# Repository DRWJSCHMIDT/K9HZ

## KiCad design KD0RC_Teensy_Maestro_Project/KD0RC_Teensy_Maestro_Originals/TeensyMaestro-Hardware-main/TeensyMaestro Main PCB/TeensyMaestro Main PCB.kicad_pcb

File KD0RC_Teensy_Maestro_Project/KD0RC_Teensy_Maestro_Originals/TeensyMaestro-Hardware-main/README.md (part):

# TeensyMaestro Front Panel and PCB

### Summary
The TeensyMaestro is a custom-built hardware controller first designed by Len (KD0RC) to interface with FlexRadio transceivers - specifically models in the 6000 and 8000 series. It performs some, but not all, of the common functions that the SmartSDR app or the Flex Maestro perform. The name TeensyMaestro comes from its core component: the Teensy 4.1 microcontroller, which powers the device. Len's initial version was built using point-to-point wiring which presents a challenge for builders. Len (KD0RC) and Simon (NV0E) have created a PCB and matching front panel that simplifies the build process. Len's documentation for hardware version 1, along with firmware that supports all versions, is available here:

[TeensyMaestro for Flex 6000 Radios](https://github.com/KD0RC/Teensy-Maestro-for-Flex-6000-radios)

The intent of this PCB is to simplify the build process, make it easier to produce a polished final product, and replace some components with less expensive alternatives.

### Main PCB

### Design Features
- A main PCB that simplifies building the Teensy Maestro and minimizes wiring errors.
- A front panel that matches the main PCB that can be fabricated by a PCB manufacturer in aluminum, with a black finish. This inexpensive option will allow a builder to achieve a refined, professional finish.
- Through-hole components to simplify assembly.
- PCB headers to connect to the rear panel connectors.
- I2C bus header for future extensibility.
- Optocoupler on key-out connector for electrical isolation from the radio.
- Reduced BOM cost due to part substitution.

### Schematic Design

[Schematic Design](https://github.com/rimuadmin/TeensyMaestro-Hardware/blob/main/TeensyMaestro%20Main%20PCB/TeensyMaestro%20Main%20PCB.pdf)

### Circuit Differences from Original Design
- **Multiplexers (CD74HC5067M) → I2C I/O Expanders (MCP23008/MCP23017)** - This frees up some GPIOs on the Teensy for other uses.
- **Adafruit LCD (HX8357D) & Touch Controller (TSC2007) → ST7796S LCD** - The new LCD has an integrated touch controller, reducing cost from ~$45 to ~$19. It's also slightly larger (4.0" vs. 3.5”) but retains the same 480x320 resolution.
- **Panel-Mounted Switches → PCB-Mounted Switches** - The 4 panel mounted switches (RIT-A, XIT-A, RIT-B, XIT-B) are now directly mounted on the PCB.
- **Panel-Mounted Encoders → PCB-Mounted Encoders** - The 9 rotary encoders are now directly mounted on the PCB.
- An optocoupler has been added to the KEY OUT for electrical isolation between the TeensyMaestro and the radio.

# Ordering the PCB & Front Panel from JLCPCB

> Ordering the Main PCB and Front Panel in the same order will save on shipping costs.

### Add the Main PCB to the cart
1. Download the zip file (TeensyMaestro Main PCB/production/TeensyMaestro Main PCB_3.0.zip) from this repository to your PC
2. Open JLCPCB's web page (jlcpcb.com) in your browser
3. Click 'Order Now'
4. Use the 'Add gerber file' button to select the zip file that you downloaded
5. The order page will import the gerber files and you should see the 2D representation of the front and rear of the panel displayed.
6. JLCPCB examines the zip file and sets the Layers and Dimensions values.
7. The default quantity is 5, which is the minimum order quantity.
8. The remaining defaults don't need to be changed, but if you prefer a different color PCB you could select it here.
9. Optionally, select 'Surface Finish: LeadFree HASL'
10. Click 'Save to Cart'.

### Add the Front Panel to the cart
1. Download the zip file (TeensyMaestro Front Panel/production/TeensyMaestro_Front_Panel_v2.0.zip) from this repository to your PC.
2. Open JLCPCB's web page (jlcpcb.com) in a browser
3. Click 'Order Now'
4. Use the 'Add gerber file' button to select the zip file that you downloaded
5. The order page will import the gerber files and you should see the 2D representation of the front and rear of the panel displayed.
6. JLCPCB examines the zip file and sets the Layers and Dimensions values.
7. Select 'Base Material: Aluminum'
8. The default quantity is 5, which is the minimum order quantity.
9. Select 'PCB Color: Black'
10. Optionally, select 'Surface Finish: LeadFree HASL'
11. Select 'Mark on PCB: Remove Mark' *(If you don't remove this, the fabricator will print the order number on the front panel)*
12. Click 'Save to Cart'.

Check out and purchase the two boards.

# PCB Assembly Steps

> *Do not solder the display on to the front side of the PCB until all the components on the rear side of the PCB have been soldered. The display covers over component through-holes that can't be soldered after the display is in place.*

- The slice tuning encoders are attached directly to the front panel, with openings in the main PCB to allow the encoders to pass through.
- The front side of the PCB holds the display, encoders and push buttons.
- The reverse side of the PCB holds the Teensy 4.1 micro controller, I/O Expanders, header connectors, resistors and capacitors.

### 1. Prepare the Display

#### 1a. Remove the SD Card Holder from the Display
To fit all the necessary through-hole components onto the TeensyMaestro PCB, we had to fully utilize the available board space. One key adjustment involves removing the SD card holder that's built into the display module. There were several reasons for this:
- The SD card holder is not connected to the TeensyMaestro circuit, so it serves no functional purpose. 
- The metal casing of the SD card holder can short against the leads of through-hole components on the back of the PCB. 
- If left in place, it can cause the display to tilt or sit unevenly, making it difficult to mount the front panel flush.

**Steps to Remove the SD Card Holder:**
1. **Apply Flux** - Dab a small amount of flux on the joints to improve heat transfer and help the solder flow into the braid.
2. **Add Solder to the Joints** - Reflow the existing joints by adding a small amount of fresh solder to each one.
3. **Use Solder Wick** - Use solder wick to absorb the molten solder from each joint.
4. **Remove the Metal Cover** - While heating the corner joints with a soldering iron, gently pry up the metal cover of the SD card holder using tweezers. Don't apply excessive force or the solder pads will lift off the FR4 PCB material.
5. **Detach the Plastic Connector** - With the cover off, continue heating the pins while using tweezers to lift the plastic connector. 
6. **Clean the Area** - Use isopropyl alcohol and Q-tips to clean off any remaining flux or residue from the PCB.

#### 1b. Solder 4 Pin Header to Display
This 4-pin header is not used by the circuit, but must be added to provide mechanical support for the display on the PCB.

1. Count and mark a 4-pin section of a header strip.
2. Cut cleanly between the 4th and 5th pins.
3. Smooth edges with a file or sanding block if sharp or uneven.
4. Solder the 4 pin header to the left side of the display.
5. The pin headers on each side should now be the same height.

In this picture, the SD Card holder has been removed and the 4 pin header soldered to the left side of the display PCB:

### 2. Solder Male Headers to the Teensy 4.1

#### 2a. Prepare Two 24-Pin Headers for the Long Sides
1. Count and mark two 24-pin sections on a header strip.
2. Cut cleanly between the 24th and 25th pins.
3. Smooth edges with a file or sanding block if sharp or uneven.
4. Repeat for the second 24-pin header.

#### 2b. Create a 5-Pin Header for GND, PROG, and ON/OFF Pins
1. Count and cut a 5-pin section.
2. Check alignment: These 5 pins go on the short side of the Teensy, opposite the USB connector (above the SD card slot area).
3. Clean up the cut edge if needed.

#### 2c. Create a 1-Pin Header for VUSB
1. Cut a single pin from the strip.
2. Use pliers to gently remove any excess plastic or bent pins.

#### 2d. Solder Male Headers to the Teensy 4.1

### 3. Prepare Female Headers for the Teensy 4.1

#### 3a. Cut Two 24-Pin Female Headers
1. Count 25 pins on a header strip.
2. Cut on the 25th pin using side cutters. This preserves 24 usable sockets in the segment before the cut.
3. Trim plastic burrs from the cut end using a file or sandpaper if needed.
4. Repeat to create a second 24-pin female header.
5. Dry fit both on the long edges of the Teensy to verify alignment.

#### 3b. Cut a 5-Pin Header for GND, PROG, ON/OFF
1. Count 6 pins and cut on the 6th pin—this gives you a 5-socket segment.
2. Inspect and clean the edges to ensure all 5 sockets are usable.
3. This header will align with the 5-pin row near the SD card slot, opposite the USB port.

#### 3c. Cut a 1-Pin Header for VUSB
1. Cut on the 2nd pin to create a single-socket header.
2. Be gentle—cutting near the ends can sometimes crack or distort the housing.
3. Clean it up and confirm the pin is straight and usable.

### 4. Solder Female Headers to the PCB
1. Insert all female headers into your PCB in the correct locations.
2. Plug the Teensy into the headers (without soldering yet) to align everything flat and square.
3. Solder the headers to the PCB while the Teensy holds them in place. This helps prevent misalignment.
4. Once all headers are secure, remove the Teensy and finish your solder joints if needed.

### 5. Rear Side
1. Solder 2 x 18-pin IC sockets to the PCB. Check that the socket alignment matches the PCB footprint.
2. Solder 1 x 28-pin IC socket to the PCB. Check that the socket alignment matches the PCB footprint. Depending on the length of the socket leads, trim the leads to reduce the chance of the leads touching the back of the display.
3. Solder the opto-isolator to the PCB. Check the alignment to ensure the opto-isolator is oriented correctly.
4. Solder capacitors to the PCB.
5. Solder resistors to the PCB.
6. Solder header connectors to the PCB.

> *The 4 holes for the I2C expansion header are right next to the 4 pins for the display. Be careful to use the correct holes for the I2C connector.*

7. Carefully check all solder connections. The display will cover some components and you will not have another chance to correct some solder joints.

### 6. Front Side
1. Solder the encoders to the PCB.
2. Solder push button switches to the PCB.

### 7. Display
- *Check all rear side components have been mounted before this step.*
- Solder display to PCB. Be careful that the header pins are all evenly seated on the PCB. 

> The 4 left side pins are only required for mechanical support of the display on the PCB. If you prefer, only solder one of the four pins. If the display needs to be desoldered, there are 3 less pins to desolder.

### 8. Standoffs
- The standoffs are recommended to prevent the front panel from bowing when the small encoders are tightened against the PCB. 
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
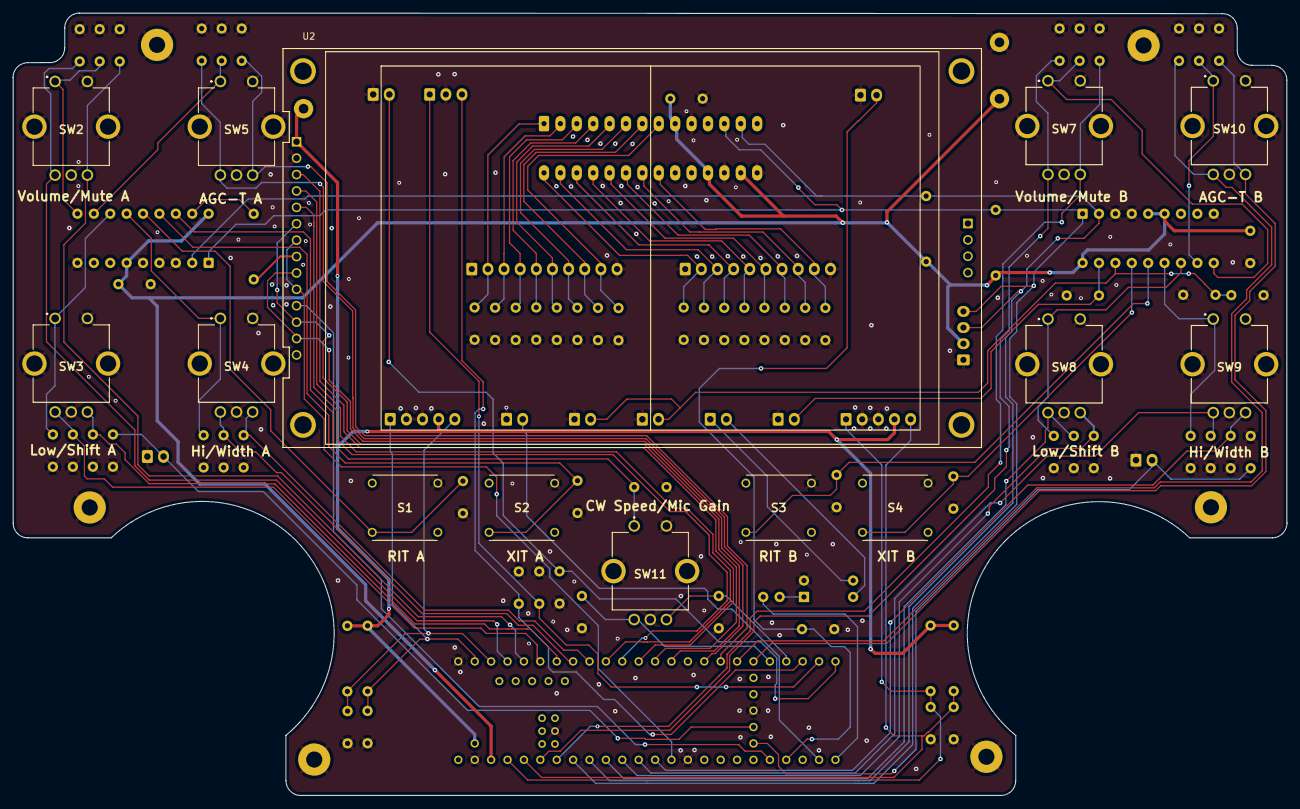
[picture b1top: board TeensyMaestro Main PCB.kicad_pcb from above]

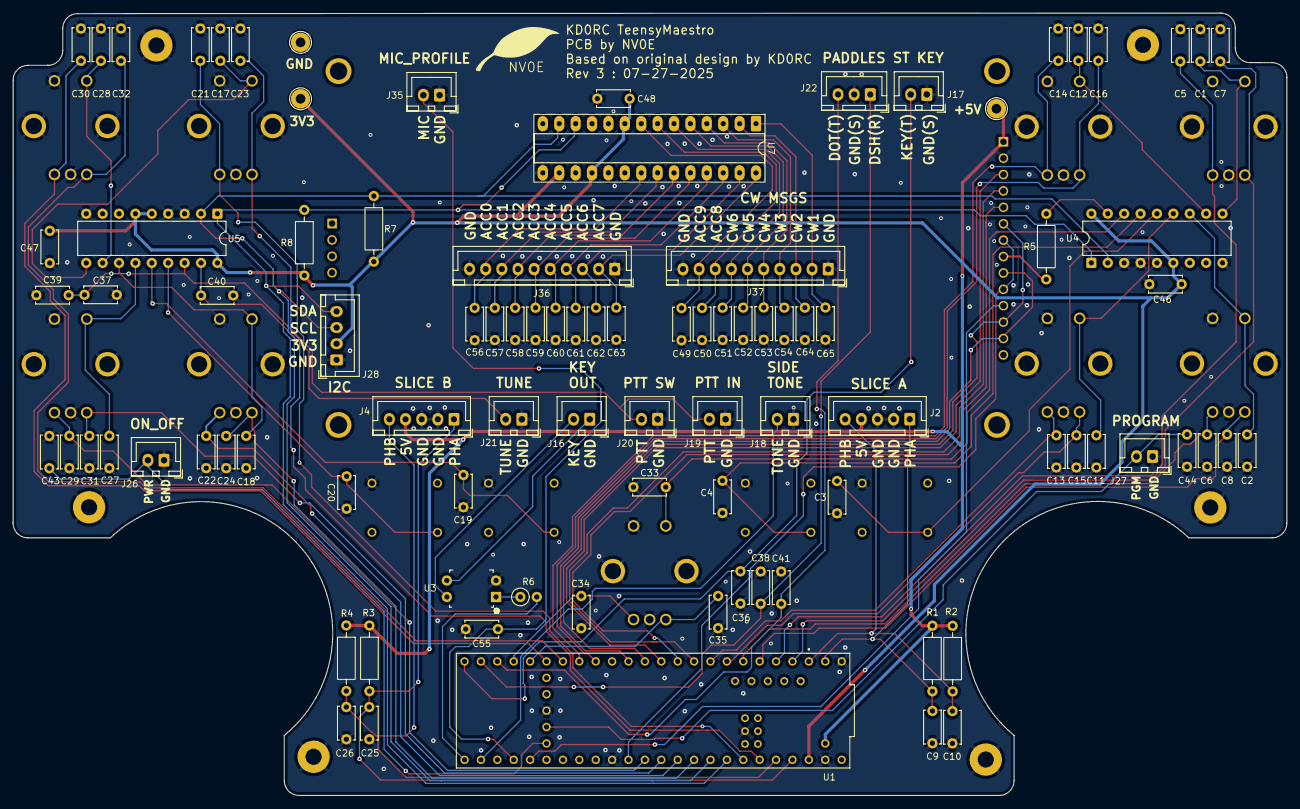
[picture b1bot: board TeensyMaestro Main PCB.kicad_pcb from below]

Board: 2 copper layers, 197.3 x 121.2 mm, 114 parts (94 on the bottom side), 78 nets.

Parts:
C1, C2, C3, C4, C5, C6, C7, C8, C9, C10, C11, C12, C13, C14, C15, C16, C17, C18, C19, C20, C21, C22, C23, C24, C25, C26, C27, C28, C29, C30, C31, C32, C33, C34, C35, C36, C37, C38, C39, C40, C41, C43, C44, C46, C47, C48, C49, C50, C51, C52, C53, C54, C55, C56, C57, C58, C59, C60, C61, C62, C63, C64, C65: 100nF; C_Disc_D5.0mm_W2.5mm_P5.00mm
H1, H2, H3, H4, H5, H6: MountingHole; MountingHole_2.5mm_Pad
J2, J4: B5B-XH-A_LF__SN_; JST_XH_B5B-XH-A_1x05_P2.50mm_Vertical
J16, J17, J18, J19, J20, J21, J26, J27, J35: B2B-XH-A_LF__SN_; JST_XH_B2B-XH-A_1x02_P2.50mm_Vertical
J22: B3B-XH-A_LF__SN_; JST_XH_B3B-XH-A_1x03_P2.50mm_Vertical
J28: B4B-PH-K-S_LF__SN_; JST_XH_B4B-XH-A_1x04_P2.50mm_Vertical
J36, J37: Conn_01x10; JST_XH_B10B-XH-A_1x10_P2.50mm_Vertical
R1, R2, R3, R4: 1K; R_Axial_DIN0207_L6.3mm_D2.5mm_P10.16mm_Horizontal
R5: 100; R_Axial_DIN0207_L6.3mm_D2.5mm_P10.16mm_Horizontal
R6: 1K; R_Axial_DIN0207_L6.3mm_D2.5mm_P2.54mm_Vertical
R7, R8: 4K7; R_Axial_DIN0207_L6.3mm_D2.5mm_P10.16mm_Horizontal
S1, S2, S3, S4: 1825910-6; 3ETH9120
SW2: RotaryEncoder_Switch_MP; PEC11L4115FS0020_NR
SW3: LowShift/NB A; PEC11L4115FS0020_NR
SW4: HighWidth/NR A; PEC11L4115FS0020_VNR
SW5: AGC-T/RIT_Sel A; PEC11L4115FS0020_VNR
SW7: Vol/Mute B; PEC11L4115FS0020_VNR
SW8: LowShift/NB B; PEC11L4115FS0020_VNR
SW9: HighWidth/NR B; PEC11L4115FS0020_NR
SW10: AGC-T/RIT_Sel A; PEC11L4115FS0020_NR
SW11: CW_Mic/Menu Sel; PEC11L4115FS0020
TP1: 5V; TestPoint_Loop_D2.54mm_Drill1.5mm_Beaded
TP2: 3V3; TestPoint_Loop_D2.54mm_Drill1.5mm_Beaded
TP3: GND; TestPoint_Loop_D2.54mm_Drill1.5mm_Beaded
U1: DEV-16771; MODULE_DEV-16771
U2: MSP4021-ST7796S; MSP4021-ST7796S-TM
U3: LTV-817; DIP-4_W7.62mm
U4, U5: MCP23008-xP; DIP-18_W7.62mm
U7: MCP23017-E_SP; DIP-28_W7.62mm_Socket_LongPads

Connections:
+3V3: C46.1, C47.1, C48.1, J28.2, R7.2, R8.2, TP2.1, U1.3.3V_2 (3.3V__1), U4.6 (~RESET), U4.18 (VDD), U5.5 (A0), U5.6 (~RESET), U5.18 (VDD), U7.9 (VDD), U7.16 (A1), U7.18 (~RESET)
+5V: J2.4, J4.4, R1.1, R2.1, R3.1, R4.1, TP1.1, U1.VUSB, U2.1 (VCC)
/IO Expander A/IOX_A_AGC-T1: C16.1, SW5.A, U1.24 (A10)
/IO Expander A/IOX_A_AGC-T2: C14.1, SW5.B, U1.25 (A11)
/IO Expander A/IOX_A_HIGH_WIDTH1: C15.1, SW4.A, U1.6 (OUT1D)
/IO Expander A/IOX_A_HIGH_WIDTH2: C13.1, SW4.B, U1.7 (RX2)
/IO Expander A/IOX_A_LOW_SHIFT1: C8.1, SW3.A, U1.4 (BCLK2)
/IO Expander A/IOX_A_LOW_SHIFT2: C6.1, SW3.B, U1.5 (IN2)
/IO Expander A/IOX_A_MUTE: C1.1, SW2.S1, U4.10 (GP0)
/IO Expander A/IOX_A_NB: C2.1, SW3.S1, U4.12 (GP2)
/IO Expander A/IOX_A_NR: C11.1, SW4.S1, U4.13 (GP3)
/IO Expander A/IOX_A_PhaseA: C9.1, J2.1, R1.2, U1.0 (RX1)
/IO Expander A/IOX_A_PhaseB: C10.1, J2.5, R2.2, U1.1 (TX1)
/IO Expander A/IOX_A_RIT: C3.1, S1.2, U4.14 (GP4)
/IO Expander A/IOX_A_RIT_SEL: C12.1, SW5.S1, U4.11 (GP1)
/IO Expander A/IOX_A_VOL1: C7.1, SW2.A, U1.2 (OUT2)
/IO Expander A/IOX_A_VOL2: C5.1, SW2.B, U1.3 (LRCLK2)
/IO Expander A/IOX_A_XIT: C4.1, S2.2, U4.15 (GP5)
/IO Expander A/MENU_SEL: C33.1, SW11.S1, U4.16 (GP6)
/IO Expander A/TFT_LED: R5.2, U4.17 (GP7)
/IO Expander B/IOX_B_AGC-T1: C32.1, SW10.A, U1.26 (A12)
/IO Expander B/IOX_B_AGC-T2: C30.1, SW10.B, U1.27 (A13)
/IO Expander B/IOX_B_HIGH_WIDTH1: C31.1, SW9.A, U1.15 (A1)
/IO Expander B/IOX_B_HIGH_WIDTH2: C29.1, SW9.B, U1.14 (A0)
/IO Expander B/IOX_B_LOW_SHIFT1: C24.1, SW8.A, U1.17 (A3)
/IO Expander B/IOX_B_LOW_SHIFT2: C22.1, SW8.B, U1.16 (A2)
/IO Expander B/IOX_B_MUTE: C17.1, SW7.S1, U5.10 (GP0)
/IO Expander B/IOX_B_NB: C18.1, SW8.S1, U5.12 (GP2)
/IO Expander B/IOX_B_NR: C27.1, SW9.S1, U5.13 (GP3)
/IO Expander B/IOX_B_PhaseA: C25.1, J4.1, R3.2, U1.23 (A9)
/IO Expander B/IOX_B_PhaseB: C26.1, J4.5, R4.2, U1.22 (A8)
/IO Expander B/IOX_B_RIT: C19.1, S3.2, U5.14 (GP4)
/IO Expander B/IOX_B_RIT_SEL: C28.1, SW10.S1, U5.11 (GP1)
/IO Expander B/IOX_B_VOL1: C23.1, SW7.A, U1.21 (A7)
/IO Expander B/IOX_B_VOL2: C21.1, SW7.B, U1.20 (A6)
/IO Expander B/IOX_B_XIT: C20.1, S4.2, U5.15 (GP5)
/IO Expander B/PTT: C37.1, C39.1, J19.2, J20.2, U5.16 (GP6)
/IO Expander B/TUNE: C40.1, J21.2, U5.17 (GP7)
/IO Expander C/ACC_0: C56.1, J36.9, U7.21 (GPA0)
/IO Expander C/ACC_1: C57.1, J36.8, U7.22 (GPA1)
/IO Expander C/ACC_2: C58.1, J36.7, U7.23 (GPA2)
/IO Expander C/ACC_3: C59.1, J36.6, U7.24 (GPA3)
/IO Expander C/ACC_4: C60.1, J36.5, U7.25 (GPA4)
/IO Expander C/ACC_5: C61.1, J36.4, U7.26 (GPA5)
/IO Expander C/ACC_6: C62.1, J36.3, U7.27 (GPA6)
/IO Expander C/ACC_7: C63.1, J36.2, U7.28 (GPA7)
/IO Expander C/ACC_8: C50.1, J37.8, U7.7 (GPB6)
/IO Expander C/ACC_9: C49.1, J37.9, U7.8 (GPB7)
/IO Expander C/CW_MSG_1: C65.1, J37.2, U7.1 (GPB0)
/IO Expander C/CW_MSG_2: C64.1, J37.3, U7.2 (GPB1)
/IO Expander C/CW_MSG_3: C54.1, J37.4, U7.3 (GPB2)
/IO Expander C/CW_MSG_4: C53.1, J37.5, U7.4 (GPB3)
/IO Expander C/CW_MSG_5: C52.1, J37.6, U7.5 (GPB4)
/IO Expander C/CW_MSG_6: C51.1, J37.7, U7.6 (GPB5)
/Mic Profile/MIC_PROFILE: C55.1, J35.2, U1.36 (CS2)
/Microcontroller/CW_MIC_MENU1: C35.1, SW11.A, U1.28 (RX7)
/Microcontroller/CW_MIC_MENU2: C34.1, SW11.B, U1.29 (TX7)
/Microcontroller/DASH: C38.1, J22.1, U1.31 (CTX3)
/Microcontroller/DOT: C41.1, J22.3, U1.30 (CRX3)
/Microcontroller/KEYOUT: R6.2, U1.33 (MCLK2)
/Microcontroller/LCD_CS: U1.10 (CS1), U2.3 (~CS)
/Microcontroller/ON_OFF: C43.1, J26.2, U1.ON/OFF
/Microcontroller/PROGRAM: C44.1, J27.2, U1.PROGRAM
/Microcontroller/SIDE_TONE: J18.2, U1.34 (RX8)
/Microcontroller/ST_KEY: C36.1, J17.2, U1.32 (OUT1B)
/Microcontroller/TFT_DC: U1.9 (OUT1C), U2.5 (D/~C)
/Microcontroller/TFT_MISO: U1.12 (MISO), U2.9 (MISO), U2.13 (T_DO)
/Microcontroller/TFT_MOSI: U1.11 (MOSI), U2.6 (MOSI), U2.12 (T_DIN)
/Microcontroller/TFT_RST: U1.8 (TX2), U2.4 (RESET)
/Microcontroller/TFT_SCK: U1.13 (SCK), U2.7 (SCK), U2.10 (T_CLK)
/Microcontroller/TOUCH_CS: U1.37 (CS3), U2.11 (T_CS)
/Miscellaneous/OPTO_COL: J16.2, U3.4
/Miscellaneous/OPTO_EMM: J16.1, U3.3
GND: C1.2, C2.2, C3.2, C4.2, C5.2, C6.2, C7.2, C8.2, C9.2, C10.2, C11.2, C12.2, C13.2, C14.2, C15.2, C16.2, C17.2, C18.2, C19.2, C20.2, C21.2, C22.2, C23.2, C24.2, C25.2, C26.2, C27.2, C28.2, C29.2, C30.2, C31.2, C32.2, C33.2, C34.2, C35.2, C36.2, C37.2, C38.2, C39.2, C40.2, C41.2, C43.2, C44.2, C46.2, C47.2, C48.2, C49.2, C50.2, C51.2, C52.2, C53.2, C54.2, C55.2, C56.2, C57.2, C58.2, C59.2, C60.2, C61.2, C62.2, C63.2, C64.2, C65.2, H1.1, H2.1, H3.1, H4.1, H5.1, H6.1, J2.2, J2.3, J4.2, J4.3, J17.1, J18.1, J19.1, J20.1, J21.1, J22.2, J26.1, J27.1, J28.1, J35.1, J36.1, J36.10, J37.1, J37.10, S1.4, S2.4, S3.4, S4.4, SW2.C, SW2.MP, SW2.S2, SW3.C, SW3.MP, SW3.S2, SW4.C, SW4.MP, SW4.S2, SW5.C, SW5.MP, SW5.S2, SW7.C, SW7.MP, SW7.S2, SW8.C, SW8.MP, SW8.S2, SW9.C, SW9.MP, SW9.S2, SW10.C, SW10.MP, SW10.S2, SW11.C, SW11.MP, SW11.S2, TP3.1, U1.GND1 (GND), U1.GND2 (GND__1), U1.GND3 (GND__2), U1.GND4 (GND__3), U1.GND5 (GND__4), U2.2 (GND), U3.2, U4.3 (A2), U4.4 (A1), U4.5 (A0), U4.9 (VSS), U5.3 (A2), U5.4 (A1), U5.9 (VSS), U7.10 (VSS), U7.15 (A0), U7.17 (A2)
I2C_SCL: J28.4, R8.1, U1.19 (A5), U4.1 (SCL), U5.1 (SCL), U7.12 (SCK)
I2C_SDA: J28.3, R7.1, U1.18 (A4), U4.2 (SDA), U5.2 (SDA), U7.13 (SDA)
unnamed: R6.1, U3.1
unnamed: R5.1, U2.8 (LED)

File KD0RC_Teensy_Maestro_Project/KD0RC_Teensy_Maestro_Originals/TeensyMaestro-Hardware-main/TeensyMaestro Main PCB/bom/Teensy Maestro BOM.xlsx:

Quantity | Designator | Description | Mouser | Digikey | Sparkfun | Other
63 | C1, C10, C11, C12, C13, C14, C15, C16, C17, C18, C19, C2, C20, C21, C22, C23, C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 | 0.1uF 50V Ceramic Leed Cap | 594-K104K15X7RF5WH5
9 | J16, J17, J18, J19, J20, J21, J26, J27, J35 | B2B-XH-A_LF__SN_ | 306-B2BXHALFSNP
2 | J2, J4 | B5B-XH-A_LF__SN_ | 306-B5BXHALFSN 306-B5BXHALFSN
1 | J22 | B3B-XH-A_LF__SN_ | 306-B3BXHALFSNP
1 | J28 | B4B-PH-K-S_LF__SN_ | 306-B4BXHALFSN
2 | J36, J37 | Conn_01x10 | 306-B10BXHALFSNP
5 | R1, R2, R3, R4, R6 | 1K Ohm 0.25W | 603-MFR-25FBF52-1K
1 | R5 | 100 Ohm 0.25W | 603-MFR-25FTF52-100R
2 | R7, R8 | 4K7 Ohm 0.25W | 603-MFR-25FRF52-4K7
4 | S1, S2, S3, S4 | SPST Momentary Switch | 642-3ETH9-12.0 | 679-3734-ND
11 | SW1, SW2, SW3, SW4, SW5, SW6, SW7, SW8, SW9, SW10, SW11 | PEC11L4115FS0020 Encoder | 652-PEC11L4115FS0020
3 | TP1, TP2, TP3 | IDC Test Pin/ Loop |  |  |  | TaydaElectronics
1 | U1 | Teensy 4.1 w/ Ethernet |  |  | DEV-16771
1 | U2 | 4" Display w/ ST7796S |  |  |  | eBay
1 | U3 | LTV-817 | 859-LTV-817
2 | U4, U5 | MCP23008-xP | 579-MCP23008-E/P
1 | U7 | MCP23017-E_SP | 579-MCP23017-E/SP

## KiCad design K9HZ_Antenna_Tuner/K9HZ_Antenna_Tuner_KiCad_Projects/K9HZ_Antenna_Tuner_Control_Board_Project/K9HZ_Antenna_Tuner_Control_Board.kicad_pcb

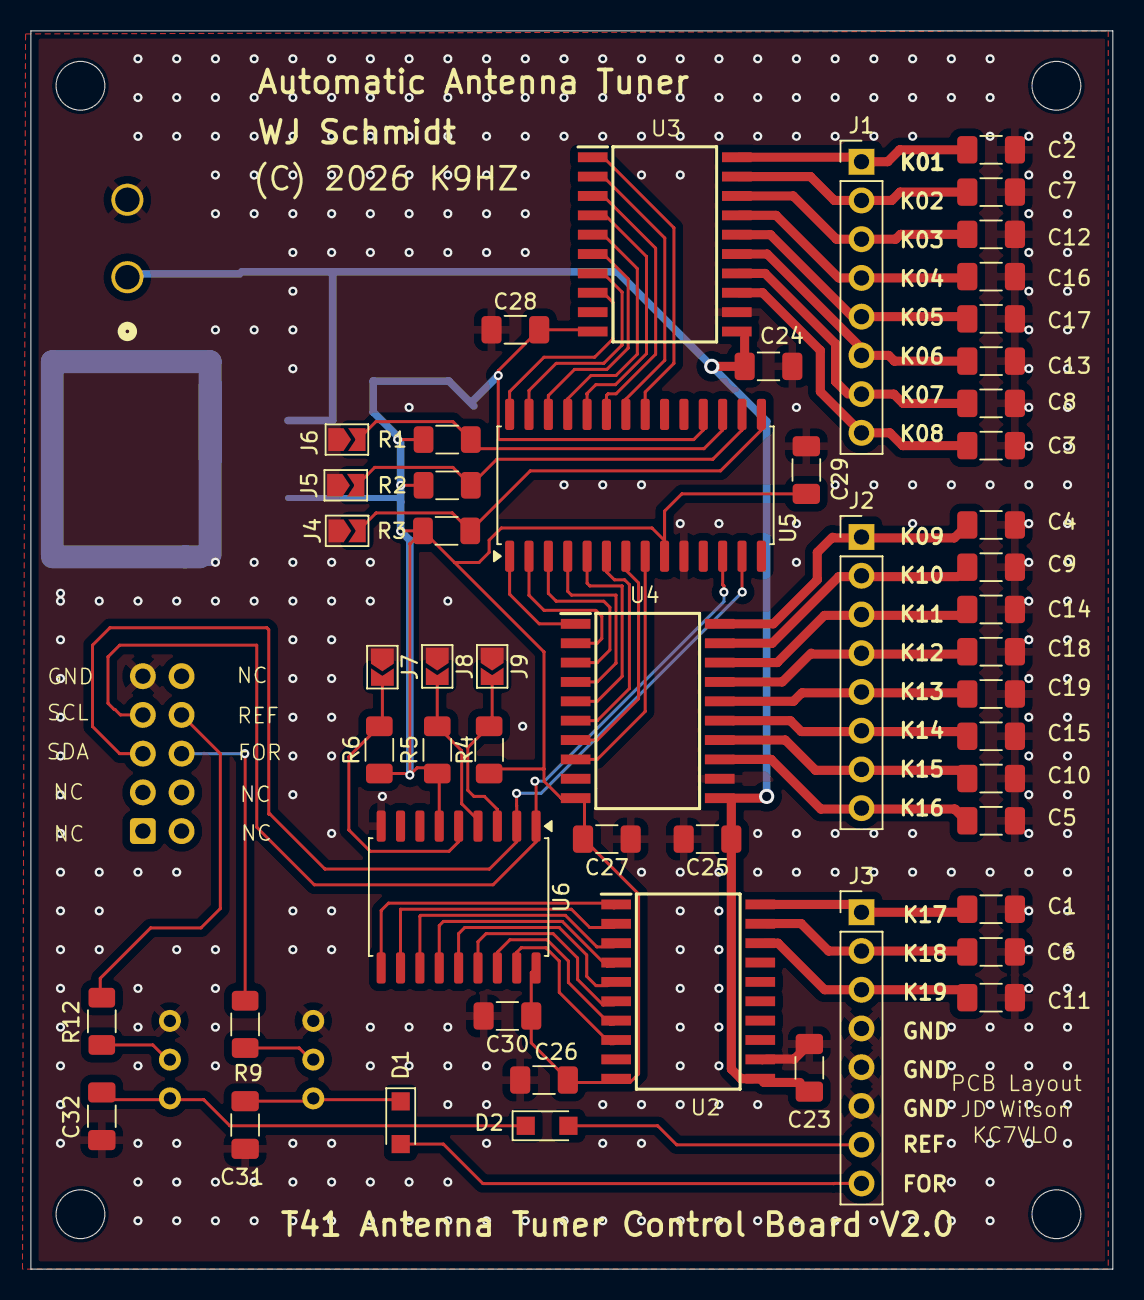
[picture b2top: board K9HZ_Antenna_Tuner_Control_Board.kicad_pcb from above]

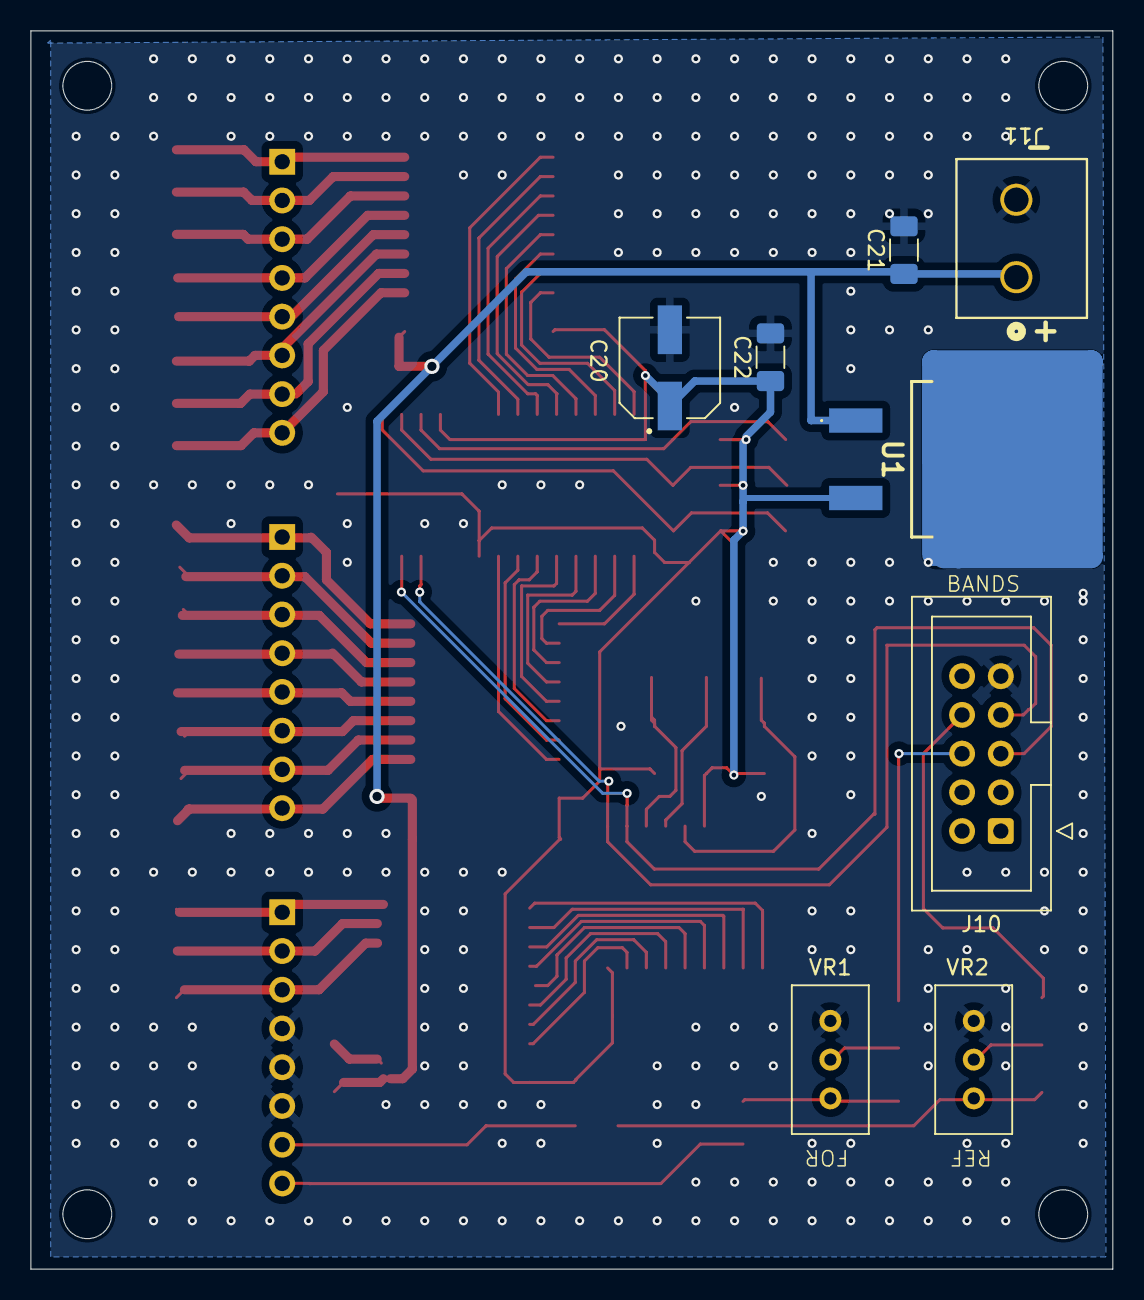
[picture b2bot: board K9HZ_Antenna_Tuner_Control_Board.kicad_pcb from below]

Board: 2 copper layers, 70.9 x 81.2 mm, 65 parts (8 on the bottom side), 62 nets.

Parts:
C1, C2, C3, C4, C5, C6, C7, C8, C9, C10, C11, C12, C13, C14, C15, C16, C17, C18, C19, C23, C24, C25, C26, C27, C28, C29, C30: 0.1uf 50V; C_1206_3216Metric_Pad1.33x1.80mm_HandSolder
C20: 220uf 16V; CAP_EEEFK1C221XP
C21: 1uf 25V; C_1206_3216Metric_Pad1.33x1.80mm_HandSolder
C22: 1uf 16V; C_1206_3216Metric_Pad1.33x1.80mm_HandSolder
C31, C32: 0.01uf 50V; C_1206_3216Metric_Pad1.33x1.80mm_HandSolder
D1, D2: BAS70H,115; Nexperia_CFP3_SOD-123W
H1, H2, H3, H4: MountingHole; MountingHole_3.2mm_M3
J1, J2, J3: 1986717-8; PinHeader_1x08_P2.54mm_Vertical
J4, J7: A0; SolderJumper-2_P1.3mm_Open_TrianglePad1.0x1.5mm
J5, J8: A1; SolderJumper-2_P1.3mm_Open_TrianglePad1.0x1.5mm
J6, J9: A2; SolderJumper-2_P1.3mm_Open_TrianglePad1.0x1.5mm
J10: IDC2x5; IDC-Header_2x05_P2.54mm_Vertical
J11: 395310002; CONN_SD-39531-003_02P_MOL
R1, R2, R3, R4, R5, R6: 3.3K; R_1206_3216Metric_Pad1.30x1.75mm_HandSolder
R9, R12: 10K; R_1206_3216Metric_Pad1.30x1.75mm_HandSolder
U1: L7805ABD2T-TR; L7805ABD2TTR
U2, U3, U4: UDN2987LWTR-6-T; SOIC127P1030X265-20N
U5: MCP23017_SO; SOIC-28W_7.5x17.9mm_P1.27mm
U6: MCP23008-E/SO; SOIC-18W_7.5x11.6mm_P1.27mm
VR1, VR2: 22k; Potentiometer_Bourns_3296W_Vertical

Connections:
+5V: C20.1, C22.1, C26.2, C27.2, C28.2, C29.1, C30.1, R1.1, R2.1, R3.1, R4.1, R5.1, R6.1, U1.3 (OUTPUT), U2.10 (OE/~R), U3.10 (OE/~R), U4.10 (OE/~R), U5.9 (VDD), U5.18 (~RESET), U6.6 (~RESET), U6.18 (VDD)
+12V: C21.1, C23.1, C24.1, C25.1, J11.1, U1.1 (INPUT), U2.11 (VS), U3.11 (VS), U4.11 (VS)
GND: C1.2, C2.2, C3.2, C4.2, C5.2, C6.2, C7.2, C8.2, C9.2, C10.2, C11.2, C12.2, C13.2, C14.2, C15.2, C16.2, C17.2, C18.2, C19.2, C20.2, C21.2, C22.2, C23.2, C24.2, C25.2, C26.1, C27.1, C28.1, C29.2, C30.2, C31.2, C32.2, J3.4, J3.5, J3.6, J4.1 (A), J5.1 (A), J6.1 (A), J7.1 (A), J8.1 (A), J9.1 (A), J10.9, J11.2, U1.2 (GND), U2.12 (GND), U3.12 (GND), U4.12 (GND), U5.10 (VSS), U6.9 (VSS), VR1.3, VR2.3
unnamed: D1.2 ((A)), J3.8
unnamed: C31.1, D1.1 ((C)), VR1.1
unnamed: D2.2 ((A)), J3.7
unnamed: C32.1, D2.1 ((C)), VR2.1
unnamed: C2.1, J1.1, U3.20 (OUT1)
unnamed: C7.1, J1.2, U3.19 (OUT2)
unnamed: C12.1, J1.3, U3.18 (OUT3)
unnamed: C16.1, J1.4, U3.17 (OUT4)
unnamed: C17.1, J1.5, U3.16 (OUT5)
unnamed: C13.1, J1.6, U3.15 (OUT6)
unnamed: C8.1, J1.7, U3.14 (OUT7)
unnamed: C3.1, J1.8, U3.13 (OUT8)
unnamed: C4.1, J2.1, U4.20 (OUT1)
unnamed: C9.1, J2.2, U4.19 (OUT2)
unnamed: C14.1, J2.3, U4.18 (OUT3)
unnamed: C18.1, J2.4, U4.17 (OUT4)
unnamed: C19.1, J2.5, U4.16 (OUT5)
unnamed: C15.1, J2.6, U4.15 (OUT6)
unnamed: C10.1, J2.7, U4.14 (OUT7)
unnamed: C5.1, J2.8, U4.13 (OUT8)
unnamed: C1.1, J3.1, U2.20 (OUT1)
unnamed: C6.1, J3.2, U2.19 (OUT2)
unnamed: C11.1, J3.3, U2.18 (OUT3)
unnamed: J4.2 (B), R3.2, U5.15 (A0)
unnamed: J5.2 (B), R2.2, U5.16 (A1)
unnamed: J6.2 (B), R1.2, U5.17 (A2)
unnamed: J7.2 (B), R6.2, U6.5 (A0)
unnamed: J8.2 (B), R5.2, U6.4 (A1)
unnamed: J9.2 (B), R4.2, U6.3 (A2)
unnamed: J10.5, U5.13 (SDA), U6.2 (SDA)
unnamed: J10.6, R9.1
unnamed: J10.7, U5.12 (SCL), U6.1 (SCL)
unnamed: J10.8, R12.1
unnamed: R9.2, VR1.2
unnamed: R12.2, VR2.2
unnamed: U2.1 (IN1), U6.10 (GP0)
unnamed: U2.2 (IN2), U6.11 (GP1)
unnamed: U2.3 (IN3), U6.12 (GP2)
unnamed: U2.4 (IN4), U6.13 (GP3)
unnamed: U2.5 (IN5), U6.14 (GP4)
unnamed: U2.6 (IN6), U6.15 (GP5)
unnamed: U2.7 (IN7), U6.16 (GP6)
unnamed: U2.8 (IN8), U6.17 (GP7)
unnamed: U3.1 (IN1), U5.21 (GPA0)
unnamed: U3.2 (IN2), U5.22 (GPA1)
unnamed: U3.3 (IN3), U5.23 (GPA2)
unnamed: U3.4 (IN4), U5.24 (GPA3)
unnamed: U3.5 (IN5), U5.25 (GPA4)
unnamed: U3.6 (IN6), U5.26 (GPA5)
unnamed: U3.7 (IN7), U5.27 (GPA6)
unnamed: U3.8 (IN8), U5.28 (GPA7)
unnamed: U4.1 (IN1), U5.1 (GPB0)
unnamed: U4.2 (IN2), U5.2 (GPB1)
unnamed: U4.3 (IN3), U5.3 (GPB2)
unnamed: U4.4 (IN4), U5.4 (GPB3)
unnamed: U4.5 (IN5), U5.5 (GPB4)
unnamed: U4.6 (IN6), U5.6 (GPB5)
unnamed: U4.7 (IN7), U5.7 (GPB6)
unnamed: U4.8 (IN8), U5.8 (GPB7)

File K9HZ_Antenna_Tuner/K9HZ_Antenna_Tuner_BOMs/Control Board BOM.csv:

#;Quantity;RefDes;Value;Name
1;1;C1;0.1uf 50V;CAP_1206
2;1;C2;0.1uf 50V;CAP_1206
3;1;C3;0.1uf 50V;CAP_1206
4;1;C4;0.1uf 50V;CAP_1206
5;1;C5;0.1uf 50V;CAP_1206
6;1;C6;0.1uf 50V;CAP_1206
7;1;C7;0.1uf 50V;CAP_1206
8;1;C8;0.1uf 50V;CAP_1206
9;1;C9;0.1uf 50V;CAP_1206
10;1;C10;0.1uf 50V;CAP_1206
11;1;C11;0.1uf 50V;CAP_1206
12;1;C12;0.1uf 50V;CAP_1206
13;1;C13;0.1uf 50V;CAP_1206
14;1;C14;0.1uf 50V;CAP_1206
15;1;C15;0.1uf 50V;CAP_1206
16;1;C16;0.1uf 50V;CAP_1206
17;1;C17;0.1uf 50V;CAP_1206
18;1;C18;0.1uf 50V;CAP_1206
19;1;C19;0.1uf 50V;CAP_1206
20;1;C20;220uf 16V;CAPAE_6.6x6.6h5.4
21;1;C21;1uF 25V;CAP_1206
22;1;C22;1uF 16V;CAP_1206
23;1;C23;0.1uf 50V;CAP_1206
24;1;C24;0.1uf 50V;CAP_1206
25;1;C25;0.1uf 50V;CAP_1206
26;1;C26;0.1uf 50V;CAP_1206
27;1;C27;0.1uf 50V;CAP_1206
28;1;C28;0.1uF 50V;CAP_1206
29;1;C29;0.1uf 50V;CAP_1206
30;1;C30;0.1uF 50V;CAP_1206
31;1;C31;0.01uF 50V;CAP_1206
32;1;C32;0.01uF 50V;CAP_1206
33;1;D1;;BAS70H,115
34;1;D2;;BAS70H,115
35;1;J1;;1986717-8
36;1;J2;;1986717-8
37;1;J3;;1986717-8
38;1;J4;;395310002
39;1;J5;BANDS;IDC2x5_Male
40;1;J6;;Solder_JMP_2
41;1;J7;;Solder_JMP_2
42;1;J8;;Solder_JMP_2
43;1;J9;;Solder_JMP_2
44;1;J10;;Solder_JMP_2
45;1;J11;;Solder_JMP_2
46;1;R1;3.3K Ohm;RES_1206
47;1;R2;3.3K Ohm;RES_1206
48;1;R3;3.3K Ohm;RES_1206
49;1;R4;3.3K Ohm;RES_1206
50;1;R5;3.3K Ohm;RES_1206
51;1;R6;3.3K Ohm;RES_1206
52;1;R7;22K;3296W
53;1;R8;52.3 Ohm;RES_1206
54;1;R9;10K;RES_0805
55;1;R10;22K;3296W
56;1;R11;52.3 Ohm;RES_1206
57;1;R12;10K;RES_1206
58;1;U1;;L7805ABD2T-TR
59;1;U2;;UDN2987LW
60;1;U3;;UDN2987LW
61;1;U4;;UDN2987LW
62;1;U5;;MCP23017_SO
63;1;U6;;MCP23008-E/SO

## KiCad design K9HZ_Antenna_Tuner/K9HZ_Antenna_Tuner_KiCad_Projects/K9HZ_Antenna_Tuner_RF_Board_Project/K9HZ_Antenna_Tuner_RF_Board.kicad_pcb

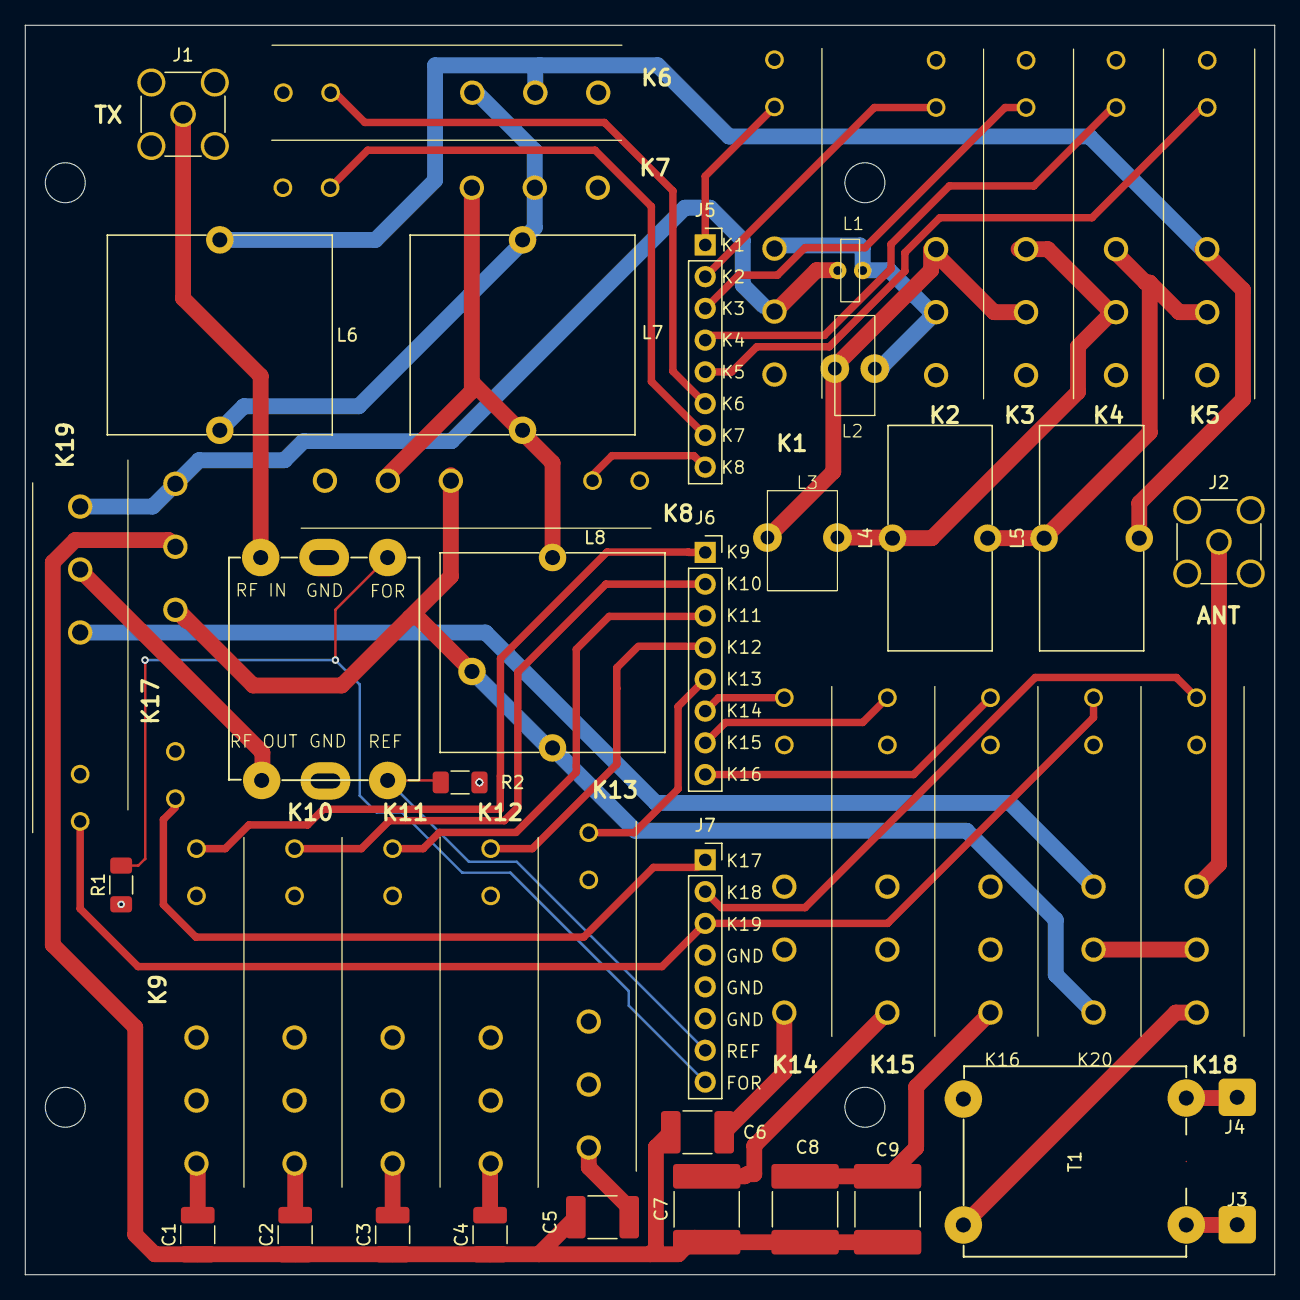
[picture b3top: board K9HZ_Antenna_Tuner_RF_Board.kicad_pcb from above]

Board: 2 copper layers, 100.0 x 100.0 mm, 52 parts (0 on the bottom side), 45 nets.

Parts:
C1: 10pF 500V; C_1210_3225Metric_Pad1.33x2.70mm_HandSolder
C2: 22pF 500V; C_1210_3225Metric_Pad1.33x2.70mm_HandSolder
C3: 47pF 500V; C_1210_3225Metric_Pad1.33x2.70mm_HandSolder
C4: 100pF 500V; C_1210_3225Metric_Pad1.33x2.70mm_HandSolder
C5: 220pF 500V; C_1812_4532Metric_Pad1.57x3.40mm_HandSolder
C6: 470pF 500V; C_1812_4532Metric_Pad1.57x3.40mm_HandSolder
C7, C8, C9: 1000pF 500V; C_2220_5750Metric_Pad1.97x5.40mm_HandSolder
H1, H2, H3, H4: MountingHole; MountingHole_3.2mm_M3
J1, J2: Conn_Coaxial; SMA_Amphenol_901-144_Vertical
J3, J4: Conn_01x01_Pin; SolderWire-0.1sqmm_1x01_D0.4mm_OD1mm
J5: 1986717-8; PinSocket_1x08_P2.54mm_Vertical
J6, J7: 1986717-8_8; PinSocket_1x08_P2.54mm_Vertical
K1, K2, K3, K4, K5, K6, K7, K8, K9, K10, K11, K12, K13, K14, K15, K16, K17, K18, K19, K20: HF41F_12-ZS; HF41F12ZS
L1: 0.05uH; L1
L2: 0.1uH; L2
L3: 0.22uH; L3
L4: 0.45uH; L_Toroid_Vertical_L17.8mm_W8.1mm_P7.62mm_Bourns_5700
L5: 1.00uH; L_Toroid_Vertical_L17.8mm_W8.1mm_P7.62mm_Bourns_5700
L6: 2.2uH; DoubleCoil
L7: 4.4uH; DoubleCoil
L8: 8.8uH; DoubleCoil
L44: Balun_5PIN_BN-43-202
R1, R2: 52.3 Ohm; R_1206_3216Metric_Pad1.30x1.75mm_HandSolder
T1: Transformer_SP_1S; Balun_5PIN_BN-43-202

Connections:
/Bypass: J7.3, K19.1 (COIL_1), K20.1 (COIL_1)
/K1.2: J5.1, K1.2 (COIL_2)
/K2.2: J5.2, K2.2 (COIL_2)
/K3.2: J5.3, K3.2 (COIL_2)
/K4.2: J5.4, K4.2 (COIL_2)
/K5.2: J5.5, K5.2 (COIL_2)
/K6.2: J5.6, K6.2 (COIL_2)
/K7.2: J5.7, K7.2 (COIL_2)
/K8.2: J5.8, K8.2 (COIL_2)
/K9.1: J6.1, K9.1 (COIL_1)
/K10.1: J6.2, K10.1 (COIL_1)
/K11.1: J6.3, K11.1 (COIL_1)
/K12.1: J6.4, K12.1 (COIL_1)
/K13.1: J6.5, K13.1 (COIL_1)
/K14.1: J6.6, K14.1 (COIL_1)
/K15.1: J6.7, K15.1 (COIL_1)
/K16.1: J6.8, K16.1 (COIL_1)
/K17.1: J7.1, K17.1 (COIL_1)
/K18.1: J7.2, K18.1 (COIL_1)
GND: J1.2 (Ext), J2.2 (Ext), J7.4, J7.5, J7.6, K1.1 (COIL_1), K2.1 (COIL_1), K3.1 (COIL_1), K4.1 (COIL_1), K5.1 (COIL_1), K6.1 (COIL_1), K7.1 (COIL_1), K8.1 (COIL_1), K9.2 (COIL_2), K9.3 (NC), K9.4 (COM), K10.2 (COIL_2), K10.3 (NC), K10.4 (COM), K11.2 (COIL_2), K11.3 (NC), K11.4 (COM), K12.2 (COIL_2), K12.3 (NC), K12.4 (COM), K13.2 (COIL_2), K13.3 (NC), K13.4 (COM), K14.2 (COIL_2), K14.3 (NC), K14.4 (COM), K15.2 (COIL_2), K15.3 (NC), K15.4 (COM), K16.2 (COIL_2), K16.3 (NC), K16.4 (COM), K17.2 (COIL_2), K18.2 (COIL_2), K19.2 (COIL_2), K20.2 (COIL_2), L44.2 (OUT), R1.1, R2.2, T1.4 (S1)
unnamed: J1.1 (In), L44.3 (COM)
unnamed: J2.1 (In), K18.3 (NC)
unnamed: J7.7, L44.6 (FWD), R2.1
unnamed: J7.8, L44.1 (IN), R1.2
unnamed: K1.4 (COM), K17.5 (NO), K19.5 (NO), L1.1
unnamed: K1.3 (NC), K2.4 (COM), L1.2, L2.1
unnamed: K2.3 (NC), K3.4 (COM), L2.2, L3.1
unnamed: K3.3 (NC), K4.4 (COM), L3.2, L4.1
unnamed: K4.3 (NC), K5.4 (COM), L4.2, L5.1
unnamed: K5.3 (NC), K6.4 (COM), L5.2, L6.1
unnamed: K6.3 (NC), K7.4 (COM), L6.2, L7.1
unnamed: K7.3 (NC), K8.4 (COM), L7.2, L8.1
unnamed: C1.2, K9.5 (NO)
unnamed: C2.2, K10.5 (NO)
unnamed: C3.2, K11.5 (NO)
unnamed: C4.2, K12.5 (NO)
unnamed: C5.2, K13.5 (NO)
unnamed: C6.2, K14.5 (NO)
unnamed: C7.2, K15.5 (NO)
unnamed: C8.2, C9.2, K16.5 (NO)
unnamed: C1.1, C2.1, C3.1, C4.1, C5.1, C6.1, C7.1, C8.1, C9.1, K17.4 (COM)
unnamed: K8.3 (NC), K17.3 (NC), K20.5 (NO), L8.2
unnamed: K18.4 (COM), K20.4 (COM)
unnamed: K19.4 (COM), L44.4 (REF)
unnamed: K19.3 (NC), K20.3 (NC)

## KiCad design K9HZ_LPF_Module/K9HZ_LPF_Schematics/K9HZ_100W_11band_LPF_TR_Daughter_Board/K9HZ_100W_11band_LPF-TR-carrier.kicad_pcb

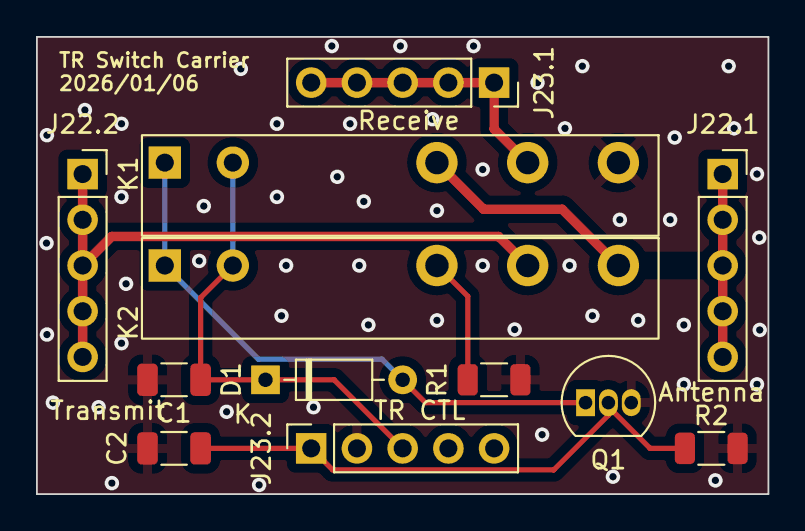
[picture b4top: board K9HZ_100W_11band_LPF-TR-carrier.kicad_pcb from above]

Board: 2 copper layers, 40.6 x 25.4 mm, 12 parts (0 on the bottom side), 8 nets.

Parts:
C1, C2: 0.1uF 50V; C_1206_3216Metric
D1: 1N4148; D_DO-35_SOD27_P7.62mm_Horizontal
J22.1: ANTENNA; PinSocket_1x05_P2.54mm_Vertical
J22.2: TRANSMIT; PinSocket_1x05_P2.54mm_Vertical
J23.1: RECEIVE; PinSocket_1x05_P2.54mm_Vertical
J23.2: TR CTL; PinSocket_1x05_P2.54mm_Vertical
K1, K2: HF41F/12-ZS; Relay_SPDT_HF41F12-ZS
Q1: BS170; TO-92_Inline
R1: 50R; R_1206_3216Metric
R2: 10k; R_1206_3216Metric

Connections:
/ANT: J22.1.1, J22.1.2, J22.1.3, J22.1.4, J22.1.5, K1.12, K2.14
/TX: C2.1, J23.2.1, Q1.2 (G), R2.1
GND: C1.2, C2.2, J23.2.2, K1.14, Q1.3 (S), R1.2, R2.2
unnamed: D1.2 (A), K1.A1, K2.A1, Q1.1 (D)
unnamed: C1.1, D1.1 (K), J23.2.3, K1.A2, K2.A2
unnamed: J22.2.1, J22.2.2, J22.2.3, J22.2.4, J22.2.5, K2.11
unnamed: J23.1.1, J23.1.2, J23.1.3, J23.1.4, J23.1.5, K1.11
unnamed: K2.12, R1.1

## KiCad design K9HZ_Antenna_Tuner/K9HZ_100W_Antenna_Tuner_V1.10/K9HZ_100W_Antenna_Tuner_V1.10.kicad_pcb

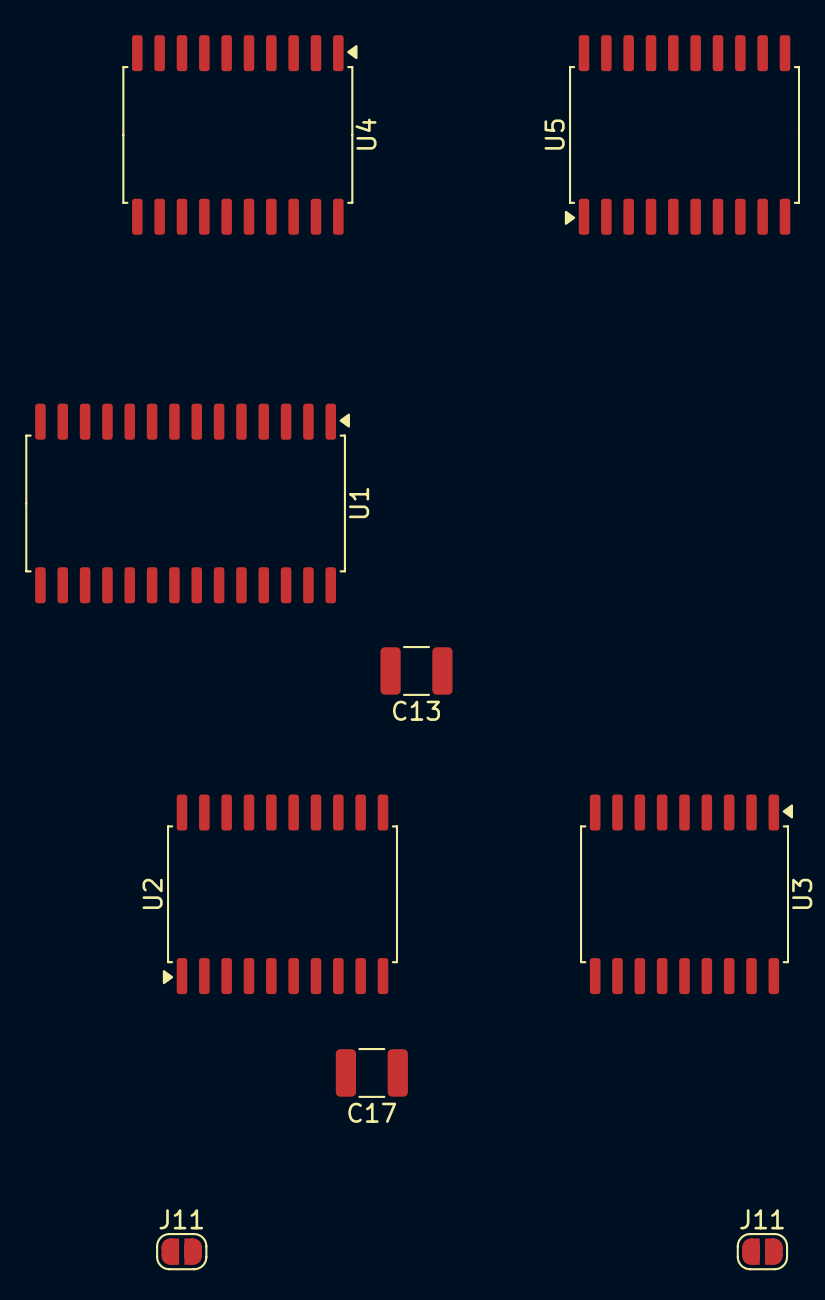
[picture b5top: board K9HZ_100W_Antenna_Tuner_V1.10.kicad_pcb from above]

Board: 2 copper layers, 9 parts (0 on the bottom side), 29 nets, no tracks yet.

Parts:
C13: 0,1uf 50V; C_1210_3225Metric
C17: 0.1uF 50V; C_1210_3225Metric
J11, J11#2: SOLDER_JMP_2; SolderJumper-2_P1.3mm_Open_RoundedPad1.0x1.5mm
U1: MCP23017_SO; SOIC-28W_7.5x17.9mm_P1.27mm
U2, U4, U5: UDN2987LW; SOIC-20W_7.5x12.8mm_P1.27mm
U3: MCP23008-E/SO; SOIC-18W_7.5x11.6mm_P1.27mm

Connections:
+5V: C17.1, U1.9 (VDD), U1.18 (~RESET), U2.10 (OE/~R), U3.6 (~RESET), U3.18 (VDD), U4.10 (OE/~R), U5.10 (OE/~R)
+12V: C13.1, U2.11 (VS), U4.11 (VS), U5.11 (VS)
GND: C13.2, C17.2, U1.10 (VSS), U2.12 (GND), U3.9 (VSS), U4.12 (GND), U5.12 (GND)
unnamed: U1.13 (SDA), U3.2 (SDA)
unnamed: U1.12 (SCL), U3.1 (SCL)
unnamed: U1.21 (GPA0), U2.1 (IN1)
unnamed: U1.22 (GPA1), U2.2 (IN2)
unnamed: U1.23 (GPA2), U2.3 (IN3)
unnamed: U1.24 (GPA3), U2.4 (IN4)
unnamed: U1.25 (GPA4), U2.5 (IN5)
unnamed: U1.26 (GPA5), U2.6 (IN6)
unnamed: U1.27 (GPA6), U2.7 (IN7)
unnamed: U1.28 (GPA7), U2.8 (IN8)
unnamed: U1.1 (GPB0), U4.1 (IN1)
unnamed: U1.2 (GPB1), U4.2 (IN2)
unnamed: U1.3 (GPB2), U4.3 (IN3)
unnamed: U1.4 (GPB3), U4.4 (IN4)
unnamed: U1.5 (GPB4), U4.5 (IN5)
unnamed: U1.6 (GPB5), U4.6 (IN6)
unnamed: U1.7 (GPB6), U4.7 (IN7)
unnamed: U1.8 (GPB7), U4.8 (IN8)
unnamed: U3.10 (GP0), U5.1 (IN1)
unnamed: U3.11 (GP1), U5.2 (IN2)
unnamed: U3.12 (GP2), U5.3 (IN3)
unnamed: U3.13 (GP3), U5.4 (IN4)
unnamed: U3.14 (GP4), U5.5 (IN5)
unnamed: U3.15 (GP5), U5.6 (IN6)
unnamed: U3.16 (GP6), U5.7 (IN7)
unnamed: U3.17 (GP7), U5.8 (IN8)

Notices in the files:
K9HZ_100W_PA_RD100HHF1_Vers/K9HZ_100W_PA_KiCAD/K9HZ_100W_KiCad/K9HZ_100W_KiCad_2.kicad_pcb:
Copyright 2024 WJ Schmidt - K9HZ
Copyright 2023
K9HZ_Antenna_Tuner/K9HZ_Antenna_Tuner_KiCad_Projects/K9HZ_Antenna_Tuner_Control_Board_Project/K9HZ_Antenna_Tuner_Control_Board.kicad_pcb:
COPYRIGHT 2025 WJ Schmidt
(C) 2026 K9HZ
K9HZ_Antenna_Tuner/K9HZ_Antenna_Tuner_KiCad_Projects/K9HZ_Antenna_Tuner_RF_Board_Project/K9HZ_Antenna_Tuner_RF_Board.kicad_pcb:
COPYRIGHT 2026 WJ Schmidt
Copyright (C) 2026
